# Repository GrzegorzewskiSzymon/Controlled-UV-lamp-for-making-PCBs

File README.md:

# Controlled-UV-lamp-for-making-PCBs

This project is originally written for ATtiny2313A with external 16MHz oscilator.

PWM signal on pin PB3 controlls Mosfet with controlls UV Leds.

Time and duty of PWM signal is set by encoder and shown on 2x 7 elements display

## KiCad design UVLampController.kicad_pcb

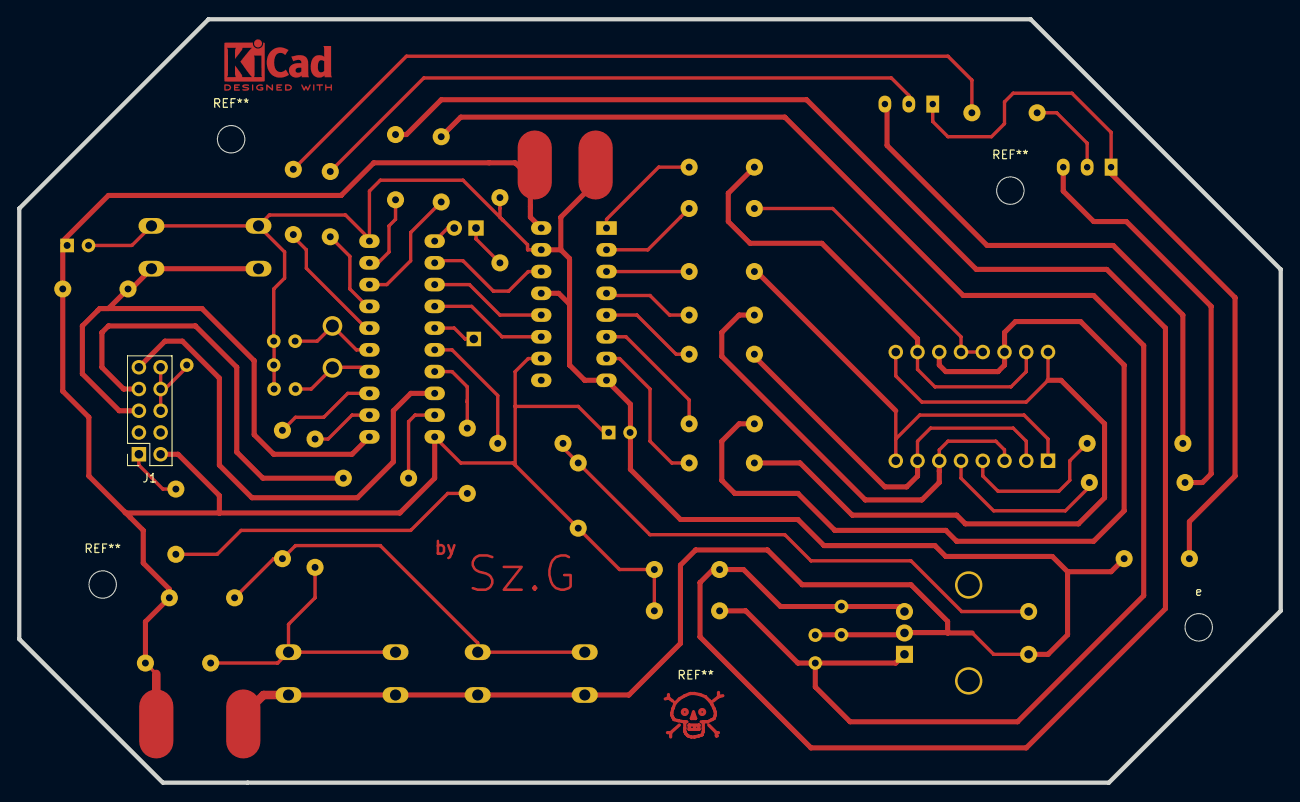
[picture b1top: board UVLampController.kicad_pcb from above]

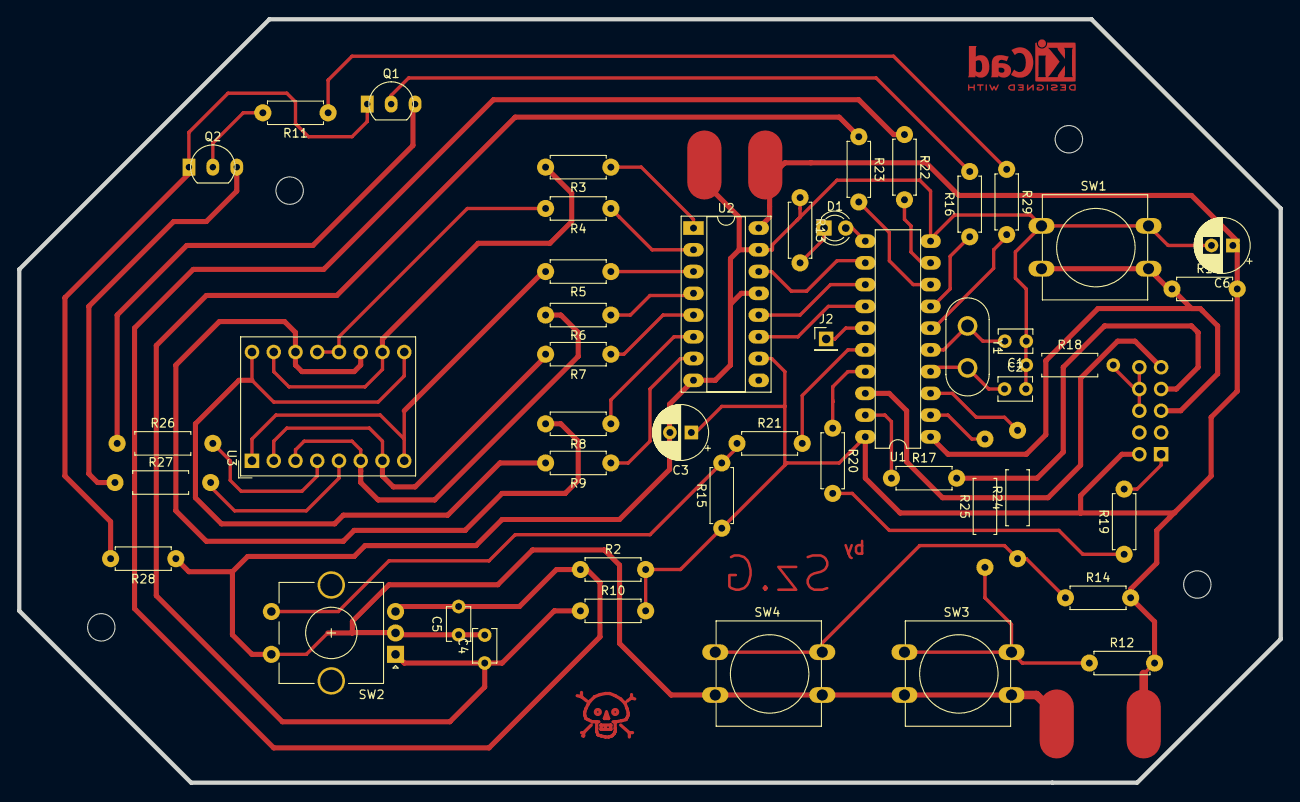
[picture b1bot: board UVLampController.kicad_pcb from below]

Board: 2 copper layers, 147.3 x 89.2 mm, 49 parts (47 on the bottom side), 52 nets.

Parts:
C1, C2: 22pF; C_Disc_D3.8mm_W2.6mm_P2.50mm
C3, C6: 220uF; CP_Radial_D6.3mm_P2.50mm
C4, C5: 473; C_Disc_D3.8mm_W2.6mm_P2.50mm
D1: LED; LED_D3.0mm
J1: 2x5_CC; PinSocket_2x05_P2.54mm_Vertical
J2: Conn_01x01_Male; PinHeader_1x01_P2.54mm_Vertical
Q1, Q2: S8050; TO-92_Inline
R1, R2, R10, R12, R14, R15: 10k; R_Axial_DIN0207_L6.3mm_D2.5mm_P7.62mm_Horizontal
R3, R4, R5, R6, R7, R8, R9: +-200; R_Axial_DIN0207_L6.3mm_D2.5mm_P7.62mm_Horizontal
R11, R16: +-2kR; R_Axial_DIN0207_L6.3mm_D2.5mm_P7.62mm_Horizontal
R13: 330R; R_Axial_DIN0207_L6.3mm_D2.5mm_P7.62mm_Horizontal
R17, R18, R19, R20, R21, R22, R23, R24, R25, R26, R27, R28, R29: 0R; R_Axial_DIN0207_L6.3mm_D2.5mm_P7.62mm_Horizontal
SW1, SW3, SW4: SW_DPST; SW_PUSH-12mm
SW2: Rotary_Encoder_Switch; RotaryEncoder_Alps_EC11E-Switch_Vertical_H20mm_CircularMoun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
U1: ATtiny2313A-PU; DIP-20_W7.62mm
U2: 74HC595; DIP-16_W7.62mm_Socket_LongPads
U3: DA04-11SYKWA
Y1: 16MHz; Crystal_HC50_Vertical
e: MountingHole_3.2mm_M3

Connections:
+5V: C3.1, C6.1, J1.1, R1.2, R2.2, R10.2, R12.2, R14.2, R15.1, U1.20, U2.10, U2.16
/A: R3.2, U3.10, U3.15
/B: R4.2, U3.12, U3.13
/C: R5.2, U3.1, U3.8
/D: R6.2, U3.3, U3.6
/E: R7.2, U3.2, U3.7
/F: R8.2, U3.11, U3.14
/G: R9.2, U3.9, U3.16
/sCS: U1.13, U2.12
/sMOSI: U1.12, U2.14
/sSCK: U1.14, U2.11
GND: C1.1, C2.2, C3.2, C4.2, C5.1, C6.2, R13.1, R18.1, R28.1, SW1.1, SW2.C, SW2.S2, SW3.2, SW4.2, U1.10, U2.8, U2.13, U2.15
MISO: J1.6, U1.18
MOSI: R20.1, U1.17
unnamed: C1.2, U1.5, Y1.1
unnamed: C2.1, U1.4, Y1.2
unnamed: C4.1, R10.1, R23.1, SW2.A
unnamed: C5.2, R2.1, R22.1, SW2.B
unnamed: D1.1, R13.2
unnamed: D1.2, U1.11
unnamed: J1.3, J1.4, J1.5, R18.2
unnamed: J1.7, R17.2
unnamed: J1.10, R19.2
unnamed: J2.1, U1.15
unnamed: Q1.1, Q2.1, R28.2
unnamed: Q1.2, R16.2
unnamed: Q1.3, R26.1
unnamed: Q2.2, R11.2
unnamed: Q2.3, R27.1
unnamed: R3.1, U2.1
unnamed: R4.1, U2.2
unnamed: R5.1, U2.3
unnamed: R6.1, U2.4
unnamed: R7.1, U2.5
unnamed: R8.1, U2.6
unnamed: R9.1, U2.7
unnamed: R11.1, R29.1
unnamed: R12.1, R25.1, SW3.1
unnamed: R14.1, R24.1, SW4.1
unnamed: R15.2, R21.1, SW2.S1
unnamed: R16.1, U1.7
unnamed: R19.1, R20.2
unnamed: R21.2, U1.16
unnamed: R22.2, U1.9
unnamed: R23.2, U1.8
unnamed: R24.2, U1.3
unnamed: R25.2, U1.2
unnamed: R26.2, U3.4
unnamed: R27.2, U3.5
unnamed: R29.2, U1.6
RST: J1.8, R1.1, SW1.2, U1.1
SCK: R17.1, U1.19

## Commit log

2022-05-23 Added description
2022-05-23 Added schematics and PCB layout
